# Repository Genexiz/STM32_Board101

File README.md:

## Currently working on this Project
- I explored how to set up the board, determine trace widths for signals and power, and arrange components to ensure clean signal integrity
- I learned how to place the STM32F103C8T6 microcontroller, configure essential peripherals like USB, SWD, UART, and I2C using STM32CubeIDE, and design the power supply with an AMS1117-3.3 regulator
- I learn about peripheral things such as How to change .stp file, How to import footprint, How to edit silk screen, Positioning component with appropriate current return path
## PCB from KiCAD

## Schematic Overview

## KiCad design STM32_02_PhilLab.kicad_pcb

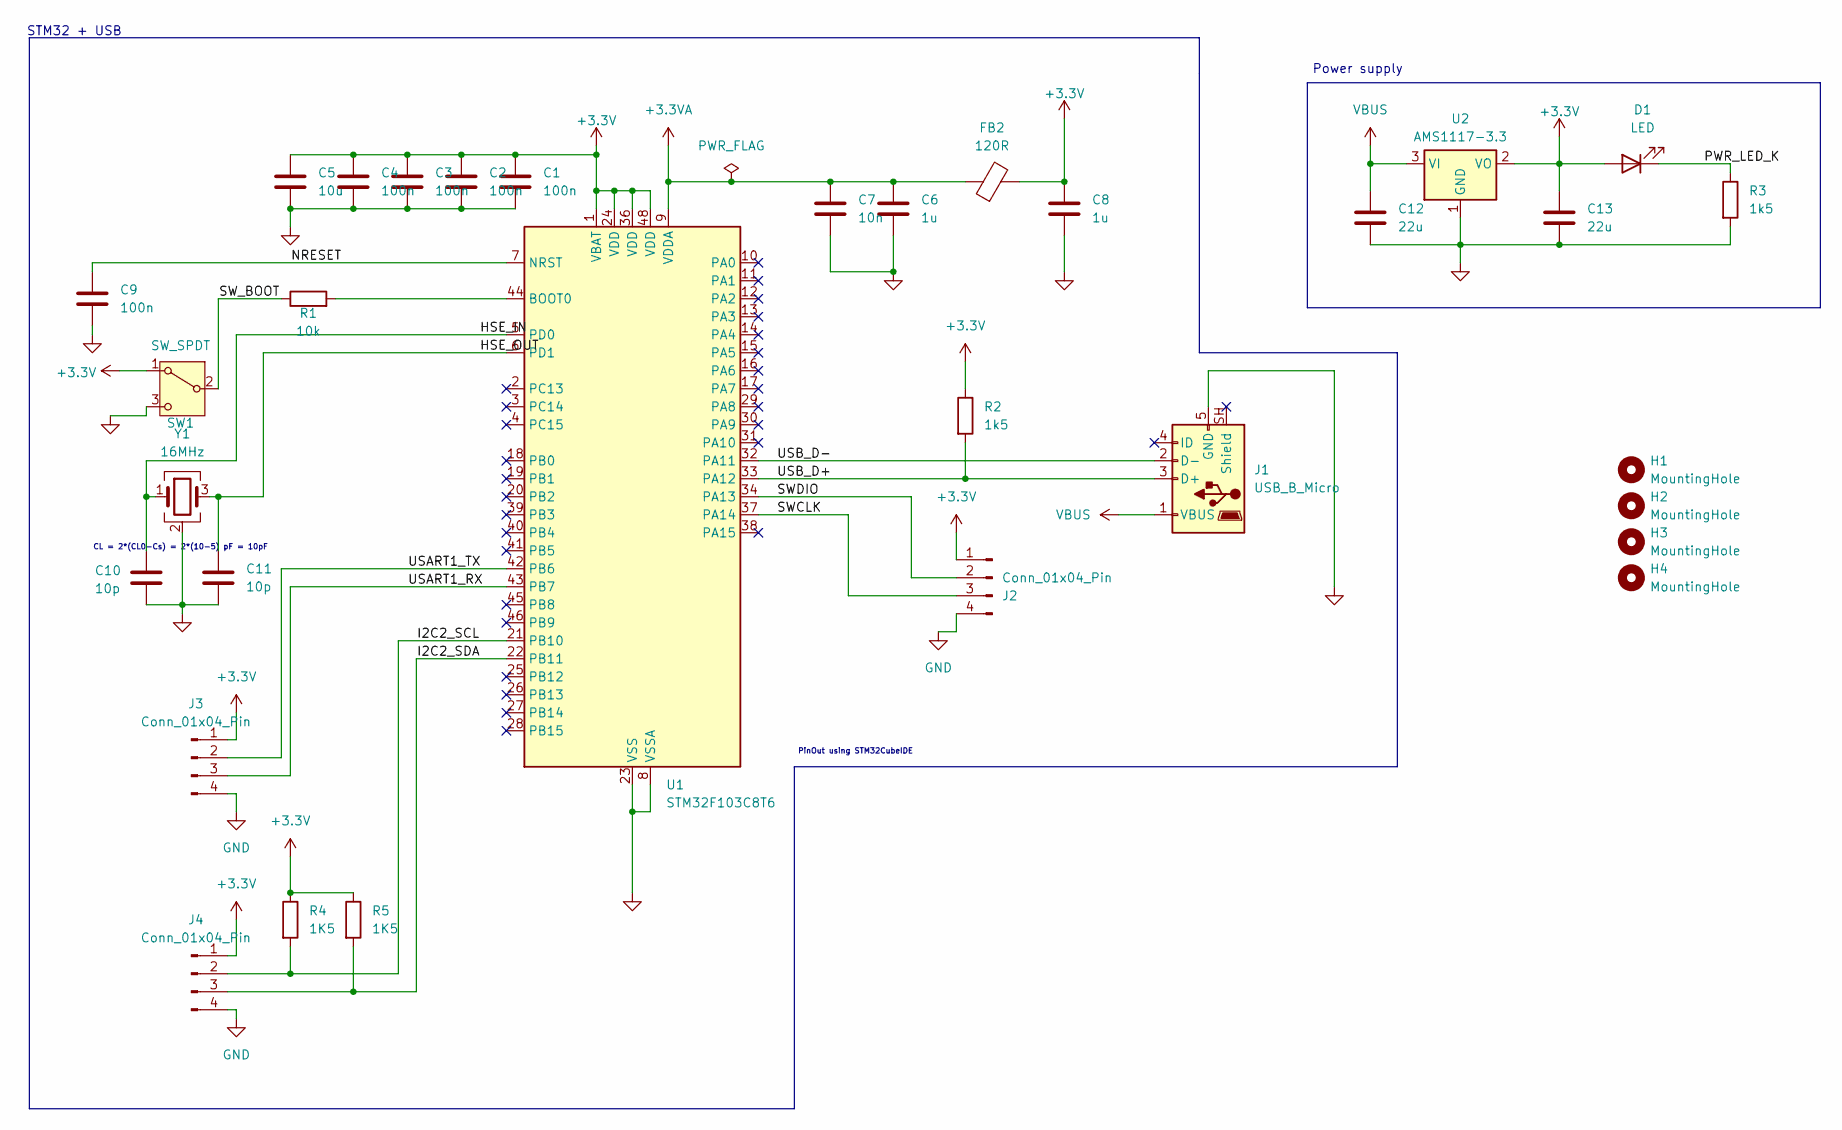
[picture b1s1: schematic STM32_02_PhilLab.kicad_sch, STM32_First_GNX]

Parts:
C1, C2, C3, C4, C9: 100n; C_0402_1005Metric
C5: 10u; C_0603_1608Metric
C6, C8: 1u; C_0402_1005Metric
C7: 10n; C_0402_1005Metric
C10, C11: 10p; C_0402_1005Metric
C12, C13: 22u; C_0805_2012Metric
D1: LED; LED_0603_1608Metric
FB2: 120R; L_0603_1608Metric
H1, H2, H3, H4: MountingHole; MountingHole_2.2mm_M2
J1: USB_B_Micro; USB_Micro-B_Wuerth_629105150521
J2, J3, J4: Conn_01x04_Pin; PinHeader_1x04_P1.00mm_Vertical
R1: 10k; R_0402_1005Metric
R2, R3: 1k5; R_0402_1005Metric
R4, R5: 1K5; R_0402_1005Metric
SW1: SW_SPDT; SW_SPDT_PCM12
U1: STM32F103C8T6; LQFP-48_7x7mm_P0.5mm
U2: AMS1117-3.3; SOT-223-3_TabPin2
Y1: 16MHz; Crystal_SMD_3225-4Pin_3.2x2.5mm

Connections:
+3.3V: C1.1, C2.1, C3.1, C4.1, C5.1, C8.1, C13.1, D1.2 (A), FB2.2, J2.1, J3.1, J4.1, R2.1, R4.1, R5.1, SW1.1 (A), U1.1 (VBAT), U1.24 (VDD), U1.36 (VDD), U1.48 (VDD), U2.2 (VO)
+3.3VA: C6.1, C7.1, FB2.1, U1.9 (VDDA)
/HSE_IN: C10.1, U1.5 (PD0), Y1.1
/HSE_OUT: C11.1, U1.6 (PD1), Y1.3
/I2C2_SCL: J4.2, R4.2, U1.21 (PB10)
/I2C2_SDA: J4.3, R5.2, U1.22 (PB11)
/NRESET: C9.1, U1.7 (NRST)
/PWR_LED_K: D1.1 (K), R3.1
/SWCLK: J2.3, U1.37 (PA14)
/SWDIO: J2.2, U1.34 (PA13)
/SW_BOOT: R1.1, SW1.2 (B)
/USART1_RX: J3.3, U1.43 (PB7)
/USART1_TX: J3.2, U1.42 (PB6)
/USB_D+: J1.3 (D+), R2.2, U1.33 (PA12)
/USB_D-: J1.2 (D-), U1.32 (PA11)
GND: C1.2, C2.2, C3.2, C4.2, C5.2, C6.2, C7.2, C8.2, C9.2, C10.2, C11.2, C12.2, C13.2, J1.5 (GND), J2.4, J3.4, J4.4, R3.2, SW1.3 (C), U1.8 (VSSA), U1.23 (VSS), U1.35 (VSS), U1.47 (VSS), U2.1 (GND), Y1.2 (G), Y1.4 (G)
unnamed: R1.2, U1.44 (BOOT0)
VBUS: C12.1, J1.1 (VBUS), U2.3 (VI)

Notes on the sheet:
Power supply
CL = 2*(CL0-Cs) = 2*(10-5) pF = 10pF
PinOut using STM32CubeIDE
STM32 + USB

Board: 2 copper layers, 32 parts (0 on the bottom side), 18 nets, no tracks yet.
